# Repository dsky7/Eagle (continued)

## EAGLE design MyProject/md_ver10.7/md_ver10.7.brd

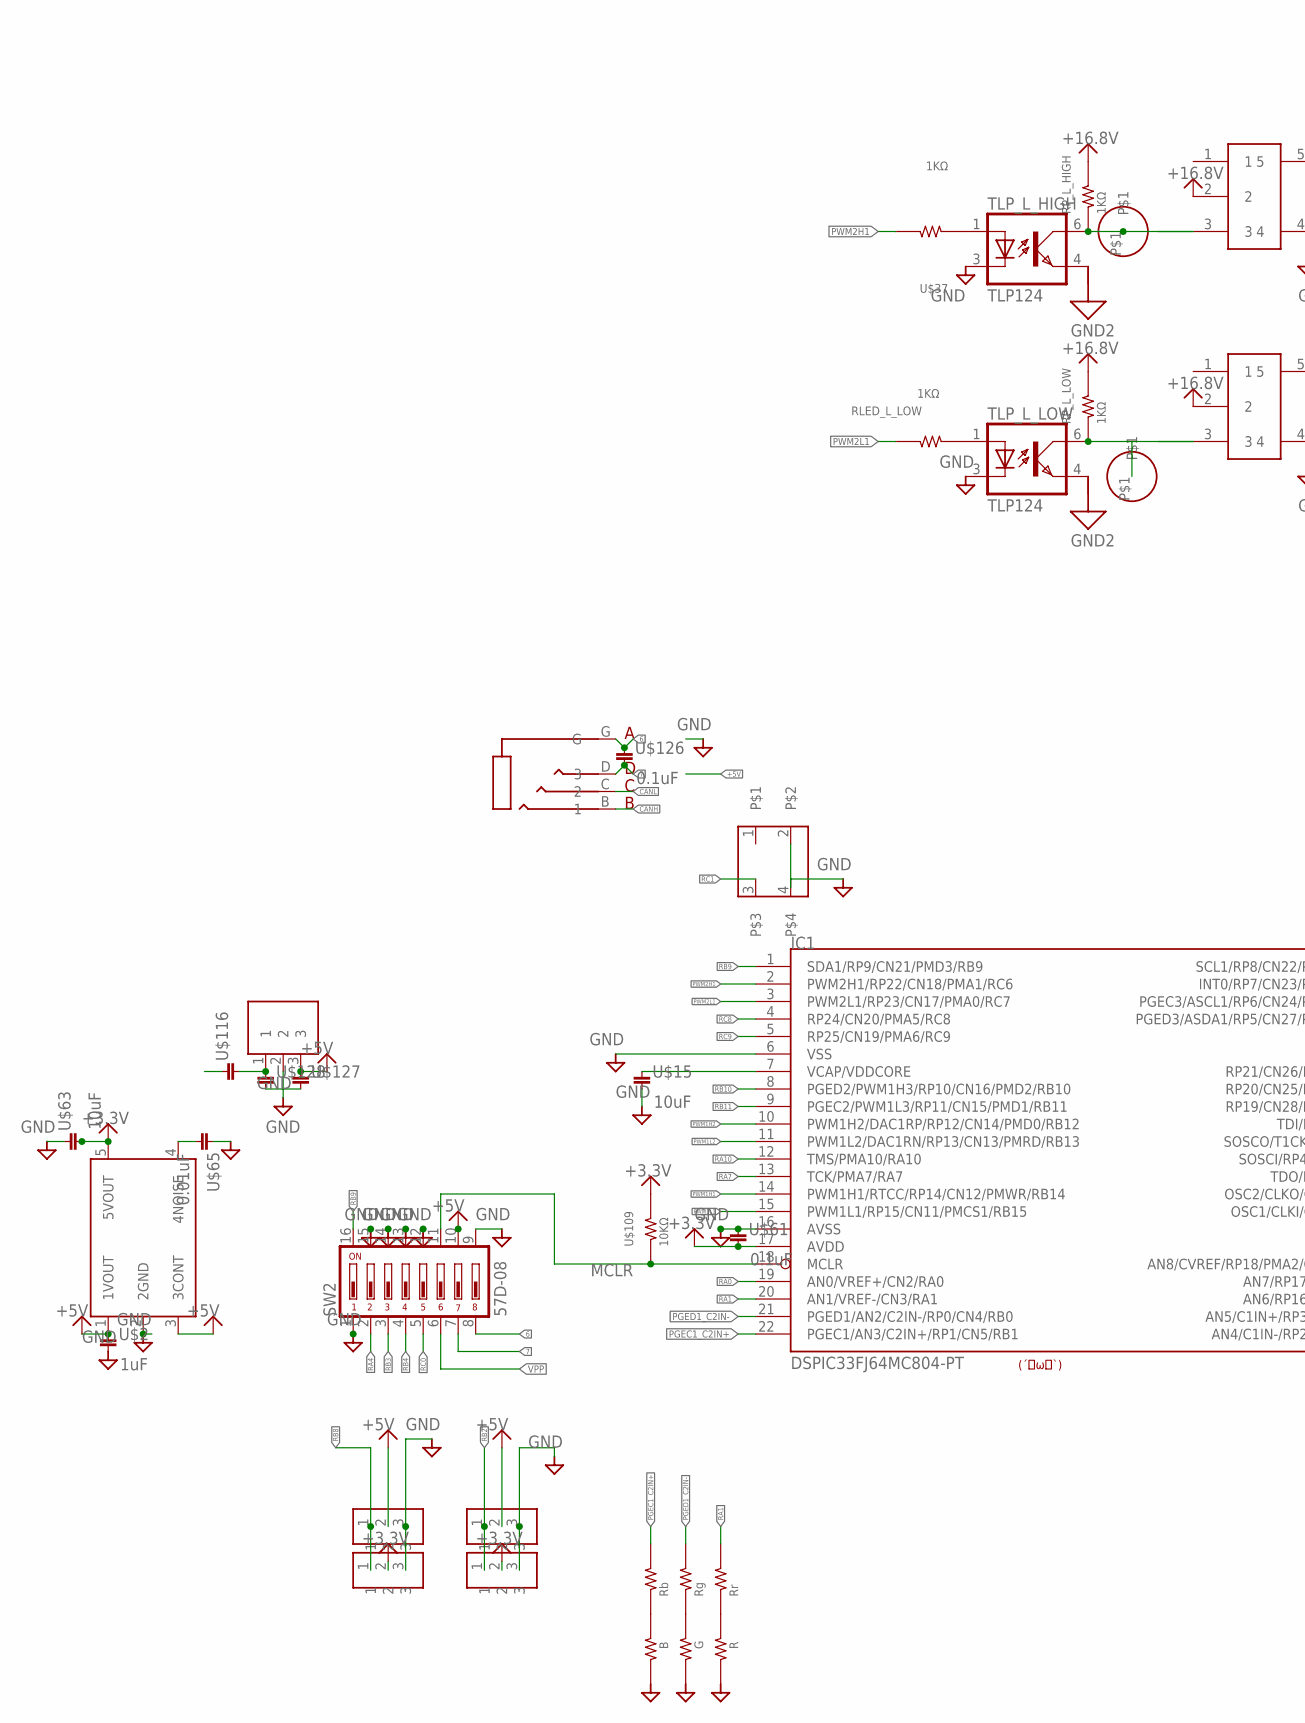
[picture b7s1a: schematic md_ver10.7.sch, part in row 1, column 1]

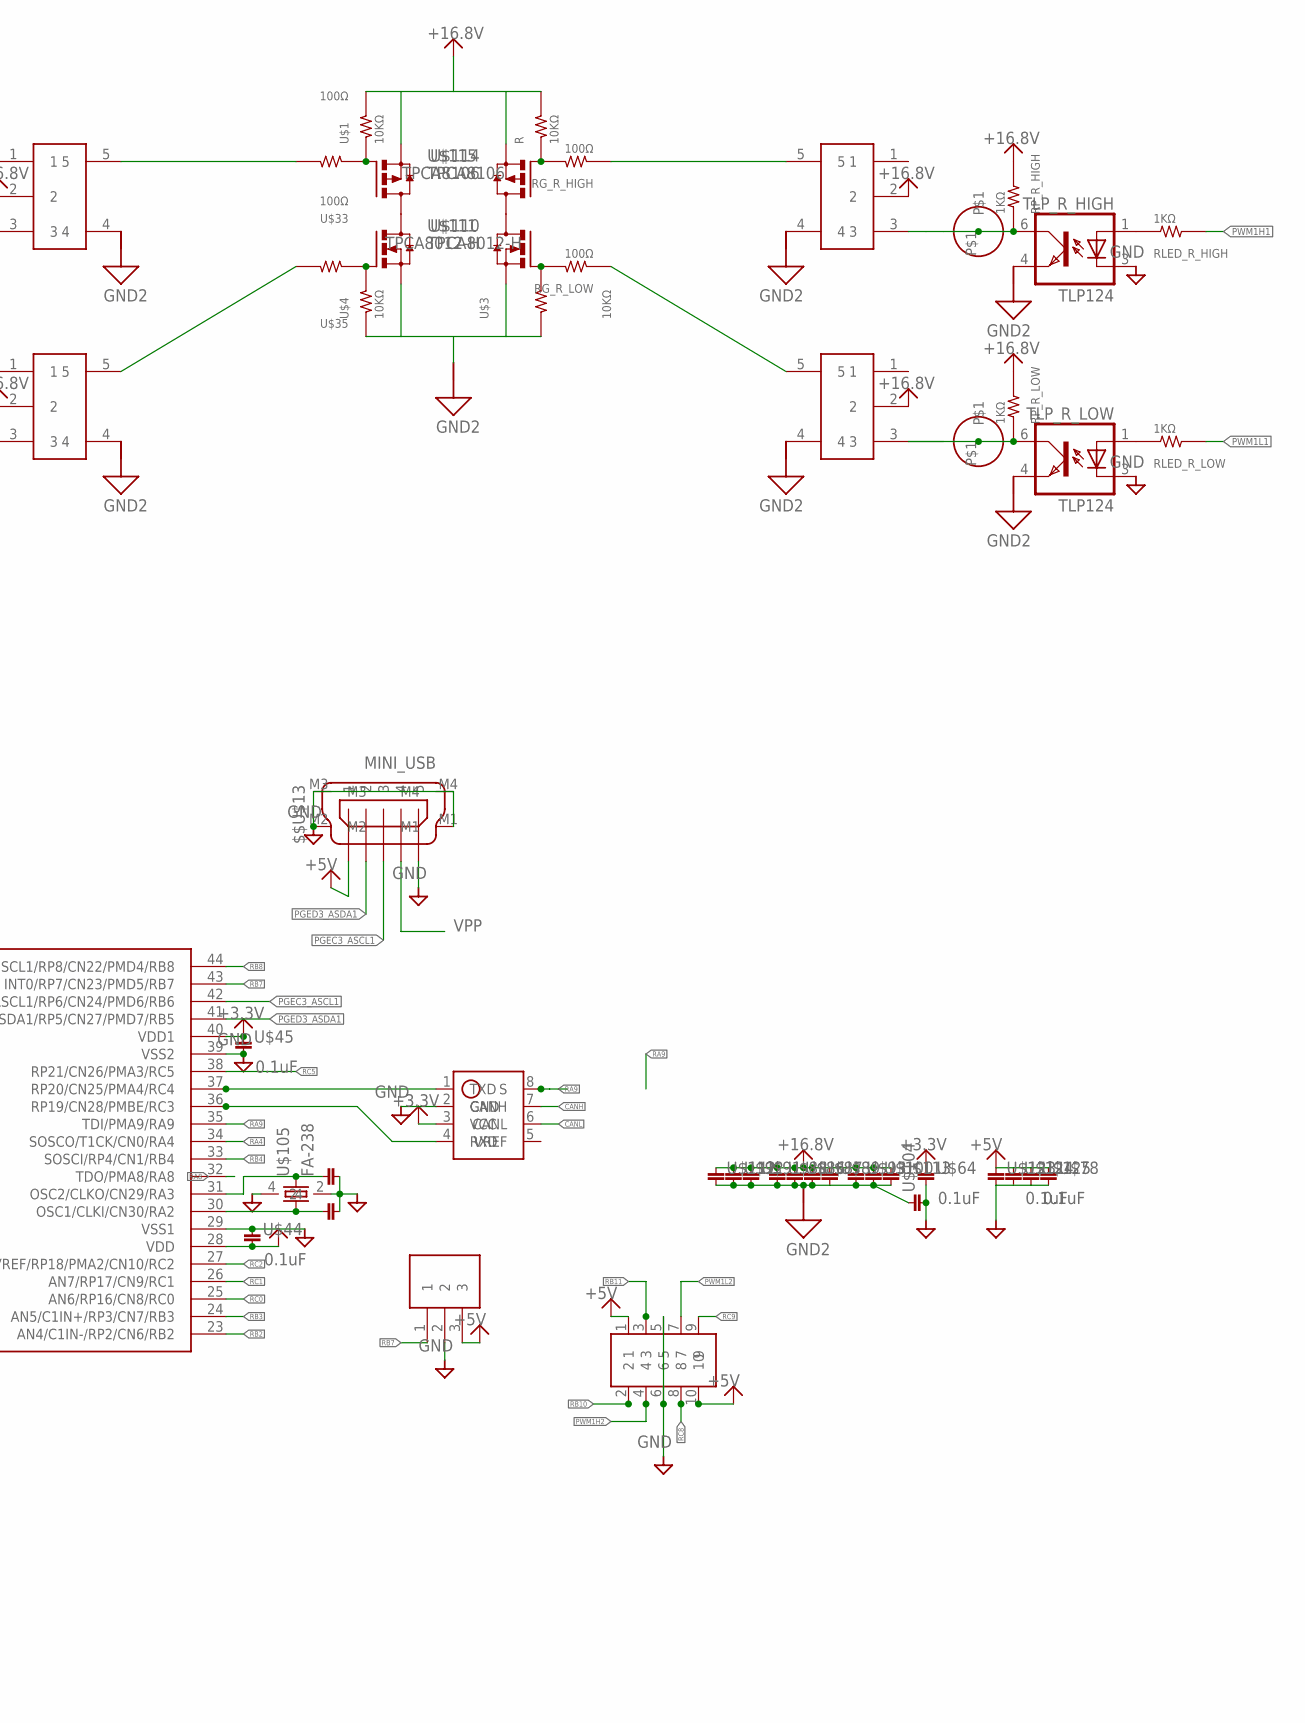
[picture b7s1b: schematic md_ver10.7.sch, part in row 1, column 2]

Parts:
$$U$5, $$U$6: PAD1_4MM
$$U$13: MINI_USB
$$U$14: AUDIO4; AUDIO4_MJ
$$U$102: 1608
$$U$108: Rr; 1608
IC1: DSPIC33FJ64MC804-PT; TQFP44
IC2: TAR5SB; SSOP5-P-0.95
IC3: SN65HVD1050; SOIC8
IC4: ＰＬ－ＩＲＭ
IC5: Ｒ－７８Ｅ５．０
IC_L_HIGH: MCP1415; SOT23-5L
IC_L_LOW: MCP1415; SOT23-5L
IC_R_HIGH: MCP1415; SOT23-5L
IC_R_LOW: MCP1415; SOT23-5L
R: 10KΩ; 1608
RG_R_HIGH: 100Ω; 1608
RG_R_LOW: 100Ω; 1608
RLED_L_LOW: 1KΩ; 1608
RLED_R_HIGH: 1KΩ; 1608
RLED_R_LOW: 1KΩ; 1608
RP_L_HIGH: 1KΩ; 1608
RP_L_LOW: 1KΩ; 1608
RP_R_HIGH: 1KΩ; 1608
RP_R_LOW: 1KΩ; 1608
SW1: TACT; TL1105
SW2: 57D-08; 57D
TLP_L_HIGH: TLP124; 11−4C1
TLP_L_LOW: TLP124; 11−4C1
TLP_R_HIGH: TLP124; 11−4C1
TLP_R_LOW: TLP124; 11−4C1
U$1, U$3, U$4, U$109: 10KΩ; 1608
U$2: 1uF; 1608
U$7, U$8: PAD1_4MM
U$9: PIN_HEADER_52; PIN_HEADER_5*2
U$10: R; 1608
U$11: G; 1608
U$12: B; 1608
U$15, U$63: 10uF; 2012
U$33, U$35: 100Ω; 1608
U$37: 1KΩ; 1608
U$44, U$45, U$61, U$64, U$124, U$125, U$126: 0.1uF; 1608
U$65: 0.01uF; 1608
U$69, U$75, U$117, U$118: 3PIN_HALF; 3PIN_INT_HALF
U$78, U$91, U$92, U$93, U$100, U$103, U$112, U$113, U$123, U$128: 1608
U$86, U$87, U$88, U$89: 3225
U$104, U$116: 2012
U$105: FA-238
U$106: Rb; 1608
U$107: Rg; 1608
U$110, U$111: TPCA8012-H; 2-5Q1A
U$114, U$115: TPCA8106; 2-5Q1A
U$127: 3216
U$129: ROGO_SYOBON

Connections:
6: $$U$14.G, SW2.8, U$126.P$1 (1)
7: $$U$14.D (3), SW2.7, U$126.P$2 (2)
+3.3V: IC1.17 (AVDD), IC1.28 (VDD), IC1.40 (VDD1), IC2.5 (5VOUT), IC3.3 (VCC), U$44.P$2 (2), U$45.P$1 (1), U$61.P$2 (2), U$63.2, U$64.P$1 (1), U$69.2, U$75.2, U$109.2
+5V: $$U$13.1, IC2.1 (1VOUT), IC2.3 (3CONT), IC4.3, IC5.3, SW2.10, U$2.P$1 (1), U$9.1, U$9.10, U$78.P$1 (1), U$117.2, U$118.2, U$123.P$1 (1), U$124.P$1 (1), U$125.P$1 (1), U$127.P$1 (1)
+16.8V: IC_L_HIGH.2, IC_L_LOW.2, IC_R_HIGH.2, IC_R_LOW.2, R.2, RP_L_HIGH.2, RP_L_LOW.2, RP_R_HIGH.2, RP_R_LOW.2, U$1.2, U$86.P$1 (1), U$87.P$1 (1), U$88.P$1 (1), U$89.P$1 (1), U$91.P$1 (1), U$92.P$1 (1), U$93.P$1 (1), U$100.P$1 (1), U$112.P$1 (1), U$113.P$1 (1), U$114.1 (S), U$114.2 (S), U$114.3 (S), U$115.1 (S), U$115.2 (S), U$115.3 (S)
CANH: $$U$14.B (1), IC3.7 (CANH)
CANL: $$U$14.C (2), IC3.6 (CANL)
GND: $$U$13.5, $$U$13.M1, $$U$13.M2, $$U$13.M3, $$U$13.M4, $$U$102.P$2 (2), IC1.6 (VSS), IC1.16 (AVSS), IC1.29 (VSS1), IC1.39 (VSS2), IC2.2 (2GND), IC3.2 (GND), IC4.2, IC5.2, SW1.2, SW1.4, SW2.1, SW2.9, SW2.12, SW2.13, SW2.14, SW2.15, TLP_L_HIGH.3 (C), TLP_L_LOW.3 (C), TLP_R_HIGH.3 (C), TLP_R_LOW.3 (C), U$2.P$2 (2), U$9.5, U$9.6, U$10.1, U$11.1, U$12.1, U$15.2, U$44.P$1 (1), U$45.P$2 (2), U$61.P$1 (1), U$63.1, U$64.P$2 (2), U$65.P$1 (1), U$69.3, U$75.3, U$78.P$2 (2), U$103.P$2 (2), U$104.2, U$105.2, U$105.4, U$117.3, U$118.3, U$123.P$2 (2), U$124.P$2 (2), U$125.P$2 (2), U$127.P$2 (2), U$128.P$2 (2)
GND2: IC_L_HIGH.4, IC_L_LOW.4, IC_R_HIGH.4, IC_R_LOW.4, TLP_L_HIGH.4 (EMIT), TLP_L_LOW.4 (EMIT), TLP_R_HIGH.4 (EMIT), TLP_R_LOW.4 (EMIT), U$3.1, U$4.1, U$86.P$2 (2), U$87.P$2 (2), U$88.P$2 (2), U$89.P$2 (2), U$91.P$2 (2), U$92.P$2 (2), U$93.P$2 (2), U$100.P$2 (2), U$104.1, U$110.1 (S), U$110.2 (S), U$110.3 (S), U$111.1 (S), U$111.2 (S), U$111.3 (S), U$112.P$2 (2), U$113.P$2 (2)
JP1: U$116.1
M1: U$111.5 (D), U$111.6 (D), U$111.7 (D), U$111.8 (D), U$115.5 (D), U$115.6 (D), U$115.7 (D), U$115.8 (D)
M2: U$110.5 (D), U$110.6 (D), U$110.7 (D), U$110.8 (D), U$114.5 (D), U$114.6 (D), U$114.7 (D), U$114.8 (D)
MCLR: IC1.18 (MCLR), SW2.11, U$109.1
unnamed: U$4.2, U$35.1, U$111.4 (G)
unnamed: IC2.4 (4NOISE), U$65.P$2 (2)
unnamed: RLED_L_LOW.1, TLP_L_LOW.1 (A)
unnamed: RG_R_LOW.2, U$3.2, U$110.4 (G)
unnamed: IC_L_HIGH.5, U$33.2
unnamed: $$U$6.P$1, IC_L_LOW.3, RP_L_LOW.1, TLP_L_LOW.6 (COL)
unnamed: IC_R_LOW.5, RG_R_LOW.1
unnamed: RLED_R_LOW.1, TLP_R_LOW.1 (A)
unnamed: TLP_L_HIGH.1 (A), U$37.1
unnamed: $$U$5.P$1, IC_L_HIGH.3, RP_L_HIGH.1, TLP_L_HIGH.6 (COL)
unnamed: $$U$102.P$1 (1), IC1.30 (OSC1/CLKI/CN30/RA2), U$105.1
unnamed: IC5.1, U$116.2, U$128.P$1 (1)
unnamed: IC_L_LOW.5, U$35.2
unnamed: IC_R_HIGH.3, RP_R_HIGH.1, TLP_R_HIGH.6 (COL), U$8.P$1
unnamed: RLED_R_HIGH.1, TLP_R_HIGH.1 (A)
unnamed: IC_R_HIGH.5, RG_R_HIGH.1
unnamed: U$1.1, U$33.1, U$115.4 (G)
unnamed: R.1, RG_R_HIGH.2, U$114.4 (G)
unnamed: U$12.2, U$106.1
unnamed: IC1.31 (OSC2/CLKO/CN29/RA3), U$103.P$1 (1), U$105.3
unnamed: U$11.2, U$107.1
unnamed: $$U$108.1, U$10.2
unnamed: IC1.37 (RP20/CN25/PMA4/RC4), IC3.1 (TXD)
unnamed: IC1.36 (RP19/CN28/PMBE/RC3), IC3.4 (RXD)
PGEC1_C2IN+: IC1.22 (PGEC1/AN3/C2IN+/RP1/CN5/RB1), U$106.2
PGEC3_ASCL1: $$U$13.3, IC1.42 (PGEC3/ASCL1/RP6/CN24/PMD6/RB6)
PGED1_C2IN-: IC1.21 (PGED1/AN2/C2IN-/RP0/CN4/RB0), U$107.2
PGED3_ASDA1: $$U$13.2, IC1.41 (PGED3/ASDA1/RP5/CN27/PMD7/RB5)
PWM1H1: IC1.14 (PWM1H1/RTCC/RP14/CN12/PMWR/RB14), RLED_R_HIGH.2
PWM1H2: IC1.10 (PWM1H2/DAC1RP/RP12/CN14/PMD0/RB12), U$9.4
PWM1L1: IC1.15 (PWM1L1/RP15/CN11/PMCS1/RB15), RLED_R_LOW.2
PWM1L2: IC1.11 (PWM1L2/DAC1RN/RP13/CN13/PMRD/RB13), U$9.7
PWM2H1: IC1.2 (PWM2H1/RP22/CN18/PMA1/RC6), U$37.2
PWM2L1: IC1.3 (PWM2L1/RP23/CN17/PMA0/RC7), RLED_L_LOW.2
RA0: IC1.19 (AN0/VREF+/CN2/RA0)
RA1: $$U$108.2, IC1.20 (AN1/VREF-/CN3/RA1)
RA4: IC1.34 (SOSCO/T1CK/CN0/RA4), SW2.2
RA7: IC1.13 (TCK/PMA7/RA7)
RA8: IC1.32 (TDO/PMA8/RA8)
RA9: IC1.35 (TDI/PMA9/RA9), IC3.8 (S)
RA10: IC1.12 (TMS/PMA10/RA10)
RB2: IC1.23 (AN4/C1IN-/RP2/CN6/RB2), U$75.1, U$118.1
RB3: IC1.24 (AN5/C1IN+/RP3/CN7/RB3), SW2.3
RB4: IC1.33 (SOSCI/RP4/CN1/RB4), SW2.4
RB7: IC1.43 (INT0/RP7/CN23/PMD5/RB7), IC4.1
RB8: IC1.44 (SCL1/RP8/CN22/PMD4/RB8), U$69.1, U$117.1
RB9: IC1.1 (SDA1/RP9/CN21/PMD3/RB9), SW2.16
RB10: IC1.8 (PGED2/PWM1H3/RP10/CN16/PMD2/RB10), U$9.2
RB11: IC1.9 (PGEC2/PWM1L3/RP11/CN15/PMD1/RB11), U$9.3
RC0: IC1.25 (AN6/RP16/CN8/RC0), SW2.5
RC1: IC1.26 (AN7/RP17/CN9/RC1), SW1.3
RC2: IC1.27 (AN8/CVREF/RP18/PMA2/CN10/RC2)
RC5: IC1.38 (RP21/CN26/PMA3/RC5)
RC8: IC1.4 (RP24/CN20/PMA5/RC8), U$9.8
RC9: IC1.5 (RP25/CN19/PMA6/RC9), U$9.9
TLP_R_LOW: IC_R_LOW.3, RP_R_LOW.1, TLP_R_LOW.6 (COL), U$7.P$1
VCAP/VDDCORE: IC1.7 (VCAP/VDDCORE), U$15.1
VPP: $$U$13.4, SW2.6

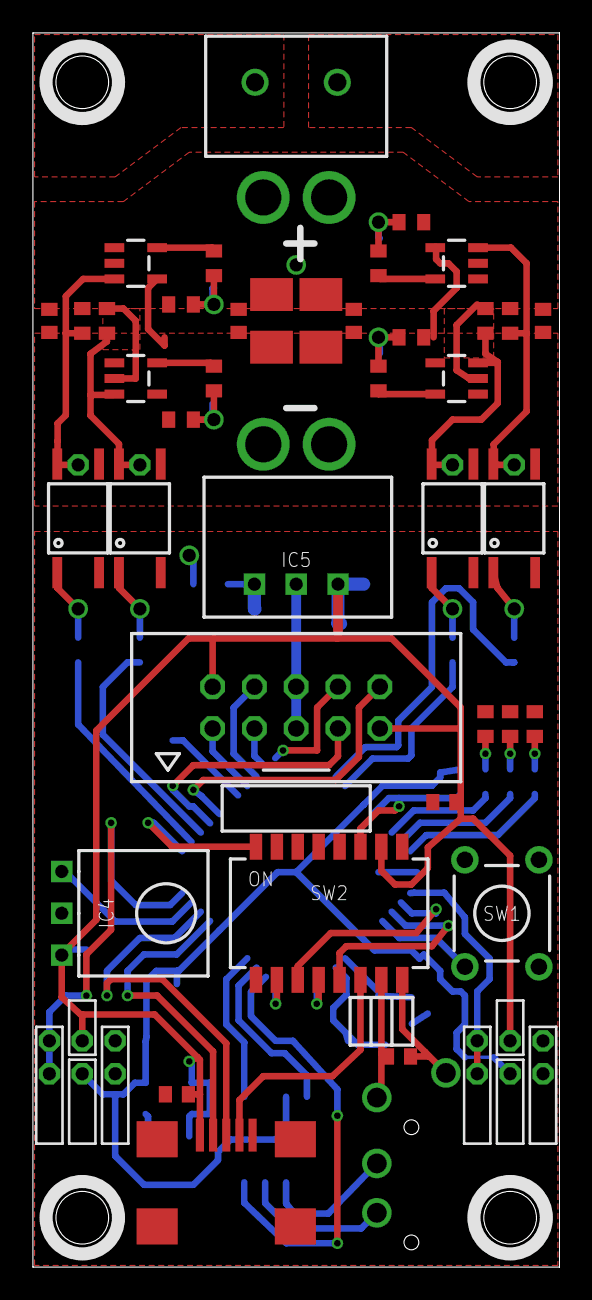
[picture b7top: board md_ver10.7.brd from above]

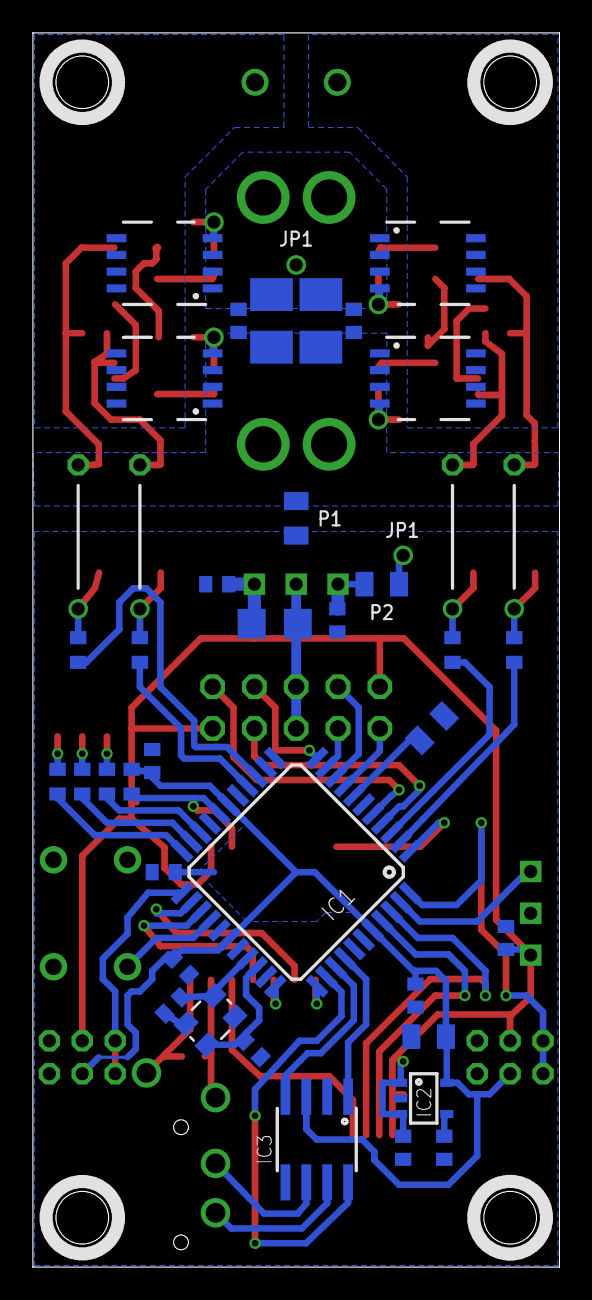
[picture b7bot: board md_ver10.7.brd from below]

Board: 2 copper layers, 32.0 x 75.0 mm, 84 parts (36 on the bottom side), 64 nets.
